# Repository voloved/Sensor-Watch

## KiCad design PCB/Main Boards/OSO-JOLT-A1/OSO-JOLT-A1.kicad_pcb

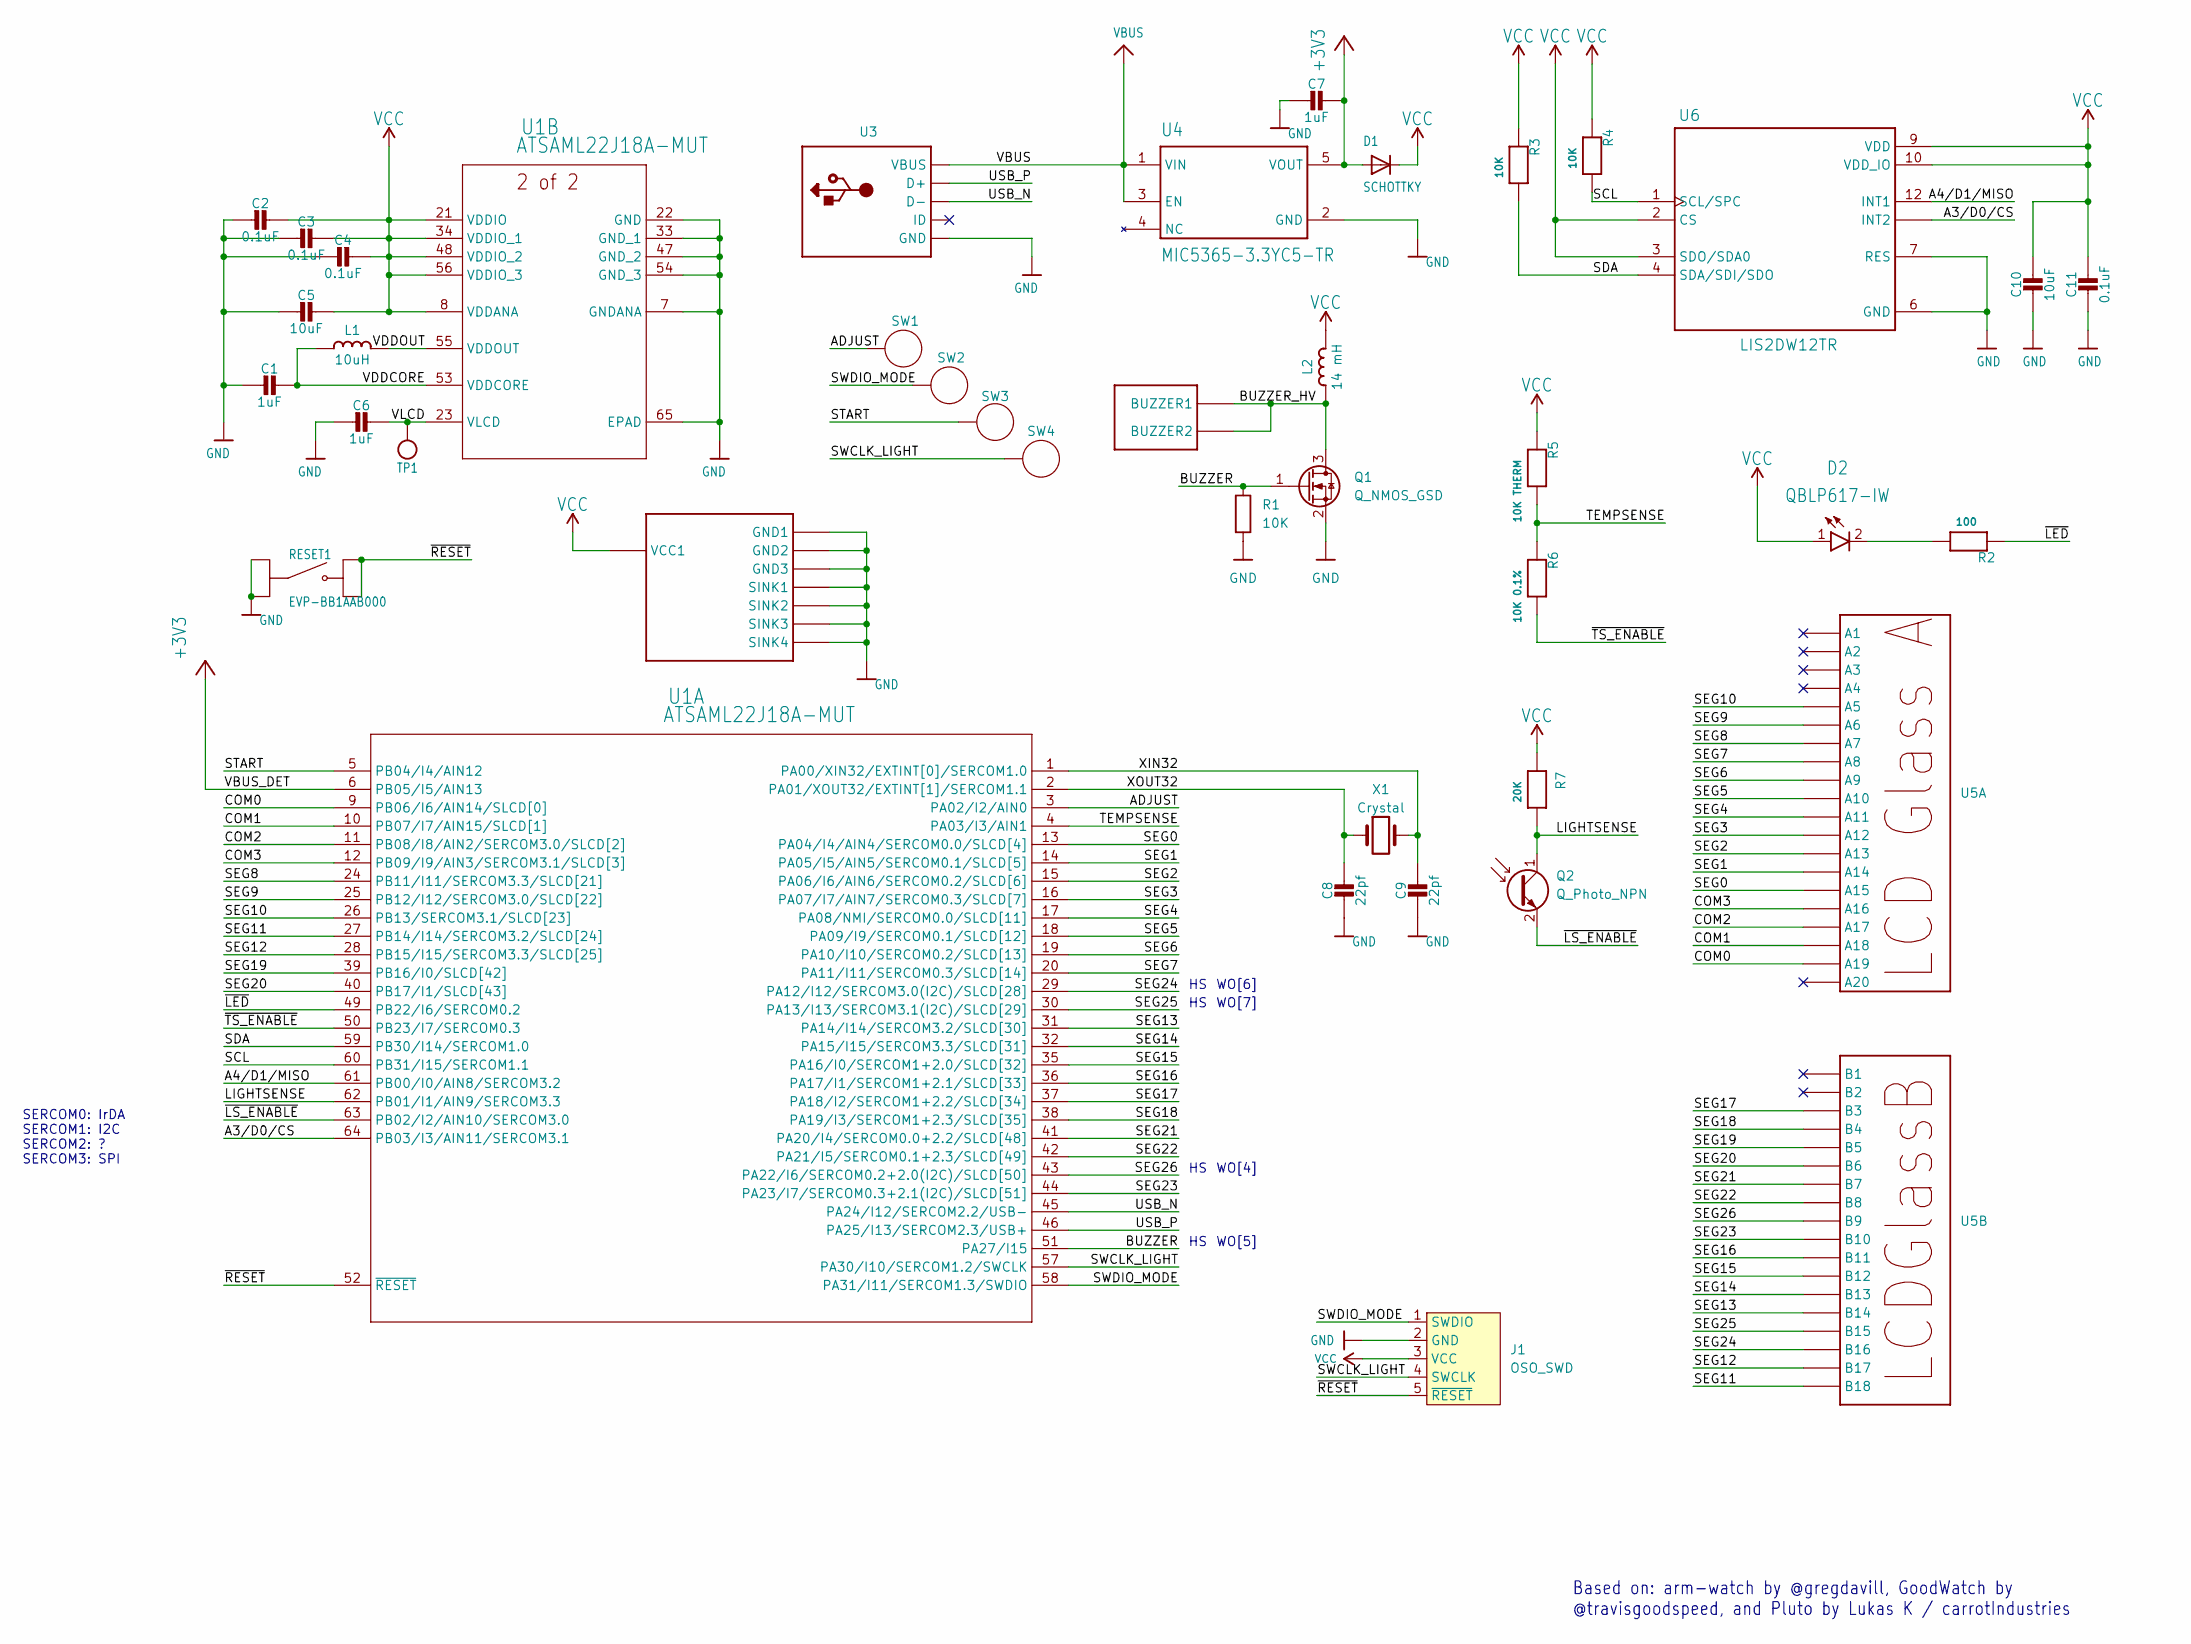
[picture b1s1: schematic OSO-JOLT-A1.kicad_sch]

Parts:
C1: 1uF; C_0805_2012Metric
C2, C4, C11: 0.1uF; C_0603_1608Metric
C3: 0.1uF; C_0201_0603Metric
C5, C10: 10uF; C_0603_1608Metric
C6, C7: 1uF; C_0603_1608Metric
C8, C9: 22pf; C_0402_1005Metric
D1: SCHOTTKY; SOD-323F
D2: QBLP617-IW; LED_QBLP617
J1: OSO_SWD; OSO_SWD_2x3
L1: 10uH; L_0805_2012Metric
L2: 14 mH; ELT3KN
Q1: Q_NMOS_GSD; SOT-523
Q2: Q_Photo_NPN; R_0603_1608Metric
R1, R3, R4: 10K; R_0201_0603Metric
R2: 100; R_0805_2012Metric
R5: 10K THERM; R_0603_1608Metric
R6: 10K 0.1%; R_0603_1608Metric
R7: 20K; R_0201_0603Metric
RESET1: EVP-BB1AAB000; SW_EVP-BB1AAB000
SW1, SW2, SW3, SW4: CASIO-DW5600-BTN
TP1: MICROBUILDER_TESTPOINTROUND1.5MM; MICROBUILDER_TESTPOINT_ROUND_1.5MM
U1: ATSAML22J18A-MUT; QFN64_9X9MC_MCH
U2: CASIO-DW5600-PWR-BUZZER
U3: CASIO-DW5600-USB
U4: MIC5365-3.3YC5-TR; SOT65P210X110-5N
U5: CASIO-DW5600-LCD
U6: LIS2DW12TR; LGA12R50P4X4_200X200X70
X1: Crystal; Crystal_SMD_3215-2Pin_3.2x1.5mm

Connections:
+3V3: C7.1, D1.A, U1.6 (PB05/I5/AIN13), U4.5 (VOUT)
/A3/D0/CS: U1.64 (PB03/I3/AIN11/SERCOM3.1), U6.11 (INT2)
/A4/D1/MISO: U1.61 (PB00/I0/AIN8/SERCOM3.2), U6.12 (INT1)
/ADJUST: SW1.BTN, U1.3 (PA02/I2/AIN0)
/BUZZER: Q1.1 (G), R1.1, U1.51 (PA27/I15)
/BUZZER_HV: L2.1, Q1.3 (D), U2.BUZZER1, U2.BUZZER2
/COM0: U1.9 (PB06/I6/AIN14/SLCD[0]), U5.A19
/COM1: U1.10 (PB07/I7/AIN15/SLCD[1]), U5.A18
/COM2: U1.11 (PB08/I8/AIN2/SERCOM3.0/SLCD[2]), U5.A17
/COM3: U1.12 (PB09/I9/AIN3/SERCOM3.1/SLCD[3]), U5.A16
/LIGHTSENSE: Q2.1 (C), R7.2, U1.62 (PB01/I1/AIN9/SERCOM3.3)
/SCL: R4.2, U1.60 (PB31/I15/SERCOM1.1), U6.1 (SCL/SPC)
/SDA: R3.2, U1.59 (PB30/I14/SERCOM1.0), U6.4 (SDA/SDI/SDO)
/SEG0: U1.13 (PA04/I4/AIN4/SERCOM0.0/SLCD[4]), U5.A15
/SEG1: U1.14 (PA05/I5/AIN5/SERCOM0.1/SLCD[5]), U5.A14
/SEG2: U1.15 (PA06/I6/AIN6/SERCOM0.2/SLCD[6]), U5.A13
/SEG3: U1.16 (PA07/I7/AIN7/SERCOM0.3/SLCD[7]), U5.A12
/SEG4: U1.17 (PA08/NMI/SERCOM0.0/SLCD[11]), U5.A11
/SEG5: U1.18 (PA09/I9/SERCOM0.1/SLCD[12]), U5.A10
/SEG6: U1.19 (PA10/I10/SERCOM0.2/SLCD[13]), U5.A9
/SEG7: U1.20 (PA11/I11/SERCOM0.3/SLCD[14]), U5.A8
/SEG8: U1.24 (PB11/I11/SERCOM3.3/SLCD[21]), U5.A7
/SEG9: U1.25 (PB12/I12/SERCOM3.0/SLCD[22]), U5.A6
/SEG10: U1.26 (PB13/SERCOM3.1/SLCD[23]), U5.A5
/SEG11: U1.27 (PB14/I14/SERCOM3.2/SLCD[24]), U5.B18
/SEG12: U1.28 (PB15/I15/SERCOM3.3/SLCD[25]), U5.B17
/SEG13: U1.31 (PA14/I14/SERCOM3.2/SLCD[30]), U5.B14
/SEG14: U1.32 (PA15/I15/SERCOM3.3/SLCD[31]), U5.B13
/SEG15: U1.35 (PA16/I0/SERCOM1+2.0/SLCD[32]), U5.B12
/SEG16: U1.36 (PA17/I1/SERCOM1+2.1/SLCD[33]), U5.B11
/SEG17: U1.37 (PA18/I2/SERCOM1+2.2/SLCD[34]), U5.B3
/SEG18: U1.38 (PA19/I3/SERCOM1+2.3/SLCD[35]), U5.B4
/SEG19: U1.39 (PB16/I0/SLCD[42]), U5.B5
/SEG20: U1.40 (PB17/I1/SLCD[43]), U5.B6
/SEG21: U1.41 (PA20/I4/SERCOM0.0+2.2/SLCD[48]), U5.B7
/SEG22: U1.42 (PA21/I5/SERCOM0.1+2.3/SLCD[49]), U5.B8
/SEG23: U1.44 (PA23/I7/SERCOM0.3+2.1(I2C)/SLCD[51]), U5.B10
/SEG24: U1.29 (PA12/I12/SERCOM3.0(I2C)/SLCD[28]), U5.B16
/SEG25: U1.30 (PA13/I13/SERCOM3.1(I2C)/SLCD[29]), U5.B15
/SEG26: U1.43 (PA22/I6/SERCOM0.2+2.0(I2C)/SLCD[50]), U5.B9
/START: SW3.BTN, U1.5 (PB04/I4/AIN12)
/SWCLK_LIGHT: J1.4 (SWCLK), SW4.BTN, U1.57 (PA30/I10/SERCOM1.2/SWCLK)
/SWDIO_MODE: J1.1 (SWDIO), SW2.BTN, U1.58 (PA31/I11/SERCOM1.3/SWDIO)
/TEMPSENSE: R5.2, R6.1, U1.4 (PA03/I3/AIN1)
/USB_N: U1.45 (PA24/I12/SERCOM2.2/USB-), U3.USB_N (D-)
/USB_P: U1.46 (PA25/I13/SERCOM2.3/USB+), U3.USB_P (D+)
/VDDCORE: C1.1, L1.1, U1.53 (VDDCORE)
/VDDOUT: L1.2, U1.55 (VDDOUT)
/VLCD: C6.1, TP1.P$1, U1.23 (VLCD)
/XIN32: C9.1, U1.1 (PA00/XIN32/EXTINT[0]/SERCOM1.0), X1.2
/XOUT32: C8.1, U1.2 (PA01/XOUT32/EXTINT[1]/SERCOM1.1), X1.1
/~LED: R2.1, U1.49 (PB22/I6/SERCOM0.2)
/~LS_ENABLE: Q2.2 (E), U1.63 (PB02/I2/AIN10/SERCOM3.0)
/~RESET: J1.5 (~RESET), RESET1.B1, RESET1.B2, U1.52 (~RESET)
/~TS_ENABLE: R6.2, U1.50 (PB23/I7/SERCOM0.3)
GND: C1.2, C2.2, C3.2, C4.2, C5.2, C6.2, C7.2, C8.2, C9.2, C10.2, C11.2, J1.2 (GND), Q1.2 (S), R1.2, RESET1.A1, RESET1.A2, U1.7 (GNDANA), U1.22 (GND), U1.33 (GND_1), U1.47 (GND_2), U1.54 (GND_3), U1.65 (EPAD), U2.GND1, U2.GND2, U2.GND3, U2.SINK1, U2.SINK2, U2.SINK3, U2.SINK4, U3.GND, U4.2 (GND), U6.6 (GND), U6.7 (RES), U6.8 (GND)
unnamed: D2.2 (C), R2.2
VBUS: U3.VBUS, U4.1 (VIN), U4.3 (EN)
VCC: C2.1, C3.1, C4.1, C5.1, C10.1, C11.1, D1.C, D2.1 (A), J1.3 (VCC), L2.2, R3.1, R4.1, R5.1, R7.1, U1.8 (VDDANA), U1.21 (VDDIO), U1.34 (VDDIO_1), U1.48 (VDDIO_2), U1.56 (VDDIO_3), U2.VCC1, U6.2 (CS), U6.3 (SDO/SDA0), U6.9 (VDD), U6.10 (VDD_IO)

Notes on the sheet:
Based on: arm-watch by @gregdavill, GoodWatch by @travisgoodspeed, and Pluto by Lukas K / carrotIndustries
WO[7]
SERCOM0: IrDA SERCOM1: I2C SERCOM2: ? SERCOM3: SPI
WO[6]
WO[4]
WO[5]

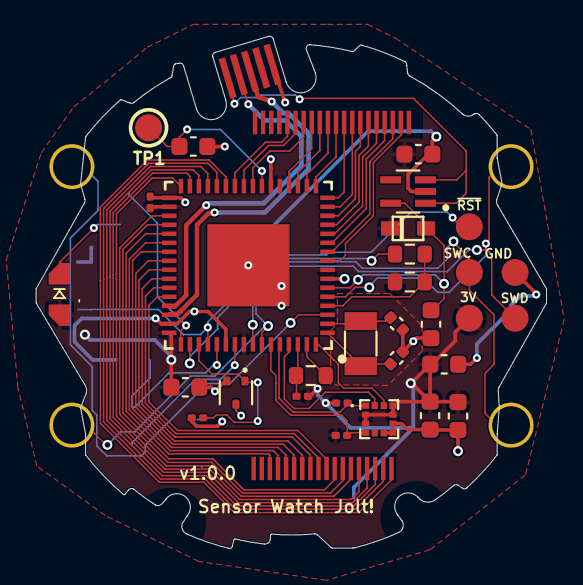
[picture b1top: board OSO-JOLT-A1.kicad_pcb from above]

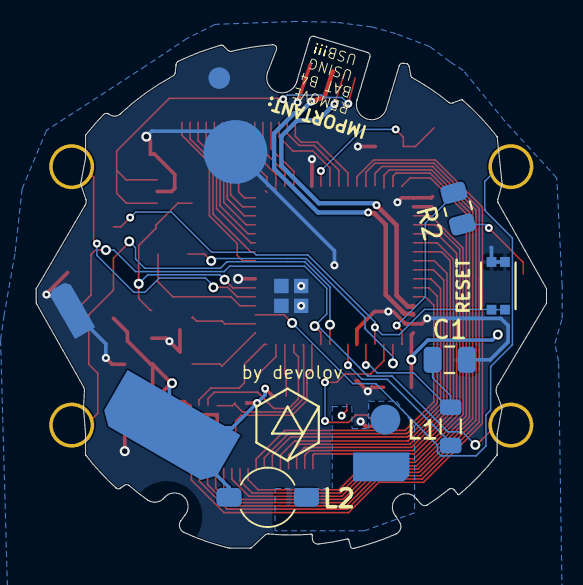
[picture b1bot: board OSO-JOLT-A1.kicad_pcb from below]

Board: 2 copper layers, 28.3 x 28.5 mm, 38 parts (5 on the bottom side), 59 nets.

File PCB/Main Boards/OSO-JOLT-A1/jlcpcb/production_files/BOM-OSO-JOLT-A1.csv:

Comment,Designator,Footprint,LCSC,Quantity
0.1uF,"C11,C2,C4",C_0603_1608Metric,C127833,3
0.1uF,C3,C_0201_0603Metric,C85923,1
100,R2,R_0805_2012Metric,C445646,1
10K,"R1,R3,R4",R_0201_0603Metric,C717002,3
10K 0.1%,R6,R_0603_1608Metric,C190610,1
10K THERM,R5,R_0603_1608Metric,C236277,1
10uF,"C10,C5",C_0603_1608Metric,C77040,2
10uH,L1,L_0805_2012Metric,C88172,1
14 mH,L2,ELT3KN,C20012585,1
1uF,C1,C_0805_2012Metric,C116352,1
1uF,"C6,C7",C_0603_1608Metric,C2167386,2
20K,R7,R_0201_0603Metric,C190611,1
22pf,"C8,C9",C_0402_1005Metric,C126502,2
ATSAML22J18A-MUT,U1,QFN64_9X9MC_MCH,C618315,1
Crystal,X1,Crystal_SMD_3215-2Pin_3.2x1.5mm,C2450269,1
EVP-BB1AAB000,RESET1,SW_EVP-BB1AAB000,C5185477,1
LIS2DW12TR,U6,LGA12R50P4X4_200X200X70,C189624,1
MIC5365-3.3YC5-TR,U4,SOT65P210X110-5N,C73103,1
QBLP617-IW,D2,LED_QBLP617,C7329223,1
Q_NMOS_GSD,Q1,SOT-523,C509959,1
Q_Photo_NPN,Q2,R_0603_1608Metric,C131276,1
SCHOTTKY,D1,SOD-323F,C119617,1

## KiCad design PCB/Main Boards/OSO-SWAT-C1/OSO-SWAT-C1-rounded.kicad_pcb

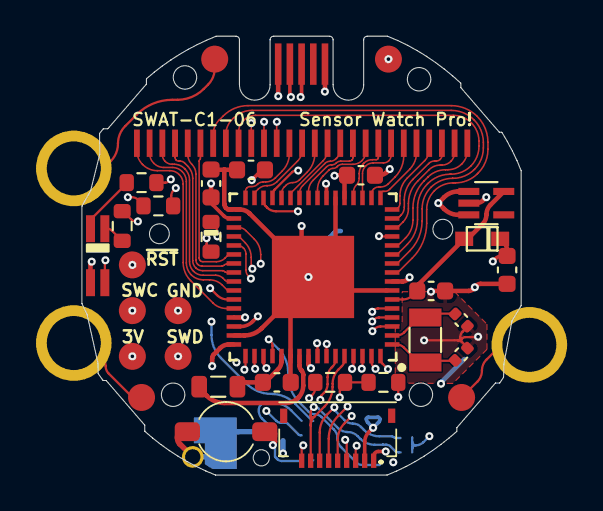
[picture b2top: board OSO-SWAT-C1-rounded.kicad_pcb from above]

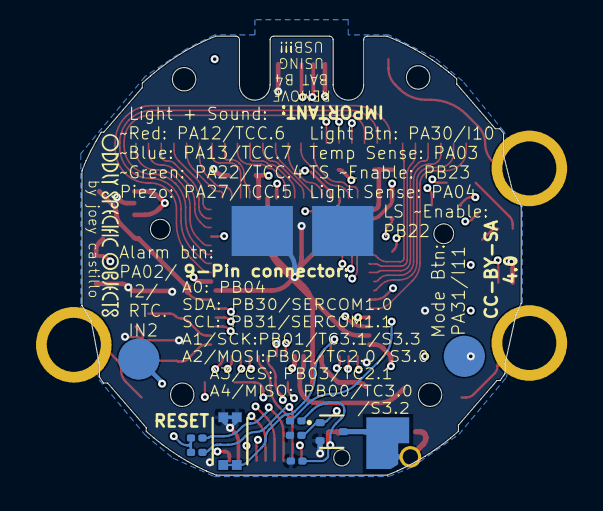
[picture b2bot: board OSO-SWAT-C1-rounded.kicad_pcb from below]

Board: 4 copper layers, 24.4 x 24.4 mm, 35 parts (7 on the bottom side), 61 nets.

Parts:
C1: 10uF; C_0603_1608Metric
C2: 0.1uF; C_0201_0603Metric
C3, C4: 0.1uF; C_0603_1608Metric
C5, C6, C9: 1uF; C_0603_1608Metric
C7, C8: 22pf; C_0402_1005Metric
D1: SCHOTTKY; SOD-323F
D2: QBLP655-RGB; LED_QBLP655_RGB
J1: OSO_SWD; OSO_SWD_2x3
J2: FH19C-9S-0.5SH_10_; FH19C9S05SH10
L1: 10uH; L_0805_2012Metric
L2: 14 mH; ELT3KN
Q1: Q_Photo_NPN; R_0603_1608Metric
Q2: Q_NMOS_GSD; SOT-523
R1, R2, R3, R4: 10K; R_0201_0603Metric
R6: 1K; R_0603_1608Metric
R7, R8: 100; R_0603_1608Metric
R10: 10K THERM; R_0603_1608Metric
R11: 10K 0.1%; R_0603_1608Metric
RESET0: EVP-BB1AAB000; SW_EVP-BB1AAB000
TP1, TP8, TP9, TP10: MICROBUILDER_TESTPOINTROUND1.5MM; MICROBUILDER_TESTPOINT_ROUND_1.5MM
U1: ATSAML22J18A-MUT; QFN64_9X9MC_MCH
U2: MIC5365-3.3YC5-TR; SOT65P210X110-5N
U$2: SENSOR-WATCH-USB; CASIO-F91W-OUTLINE-USB
X1: Crystal; Crystal_SMD_3215-2Pin_3.2x1.5mm

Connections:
+3V3: C9.1, D1.A, U1.6 (PB05/I5/AIN13), U2.5 (VOUT)
/A0: J2.9, U1.5 (PB04/I4/AIN12)
/A1_SCK: J2.6, U1.62 (PB01/I1/AIN9/SERCOM3.3)
/A2_MOSI: J2.5, U1.63 (PB02/I2/AIN10/SERCOM3.0)
/A3/D0/CS: J2.4, U1.64 (PB03/I3/AIN11/SERCOM3.1)
/A4/D1/MISO: J2.3, U1.61 (PB00/I0/AIN8/SERCOM3.2)
/ALARM: TP10.P$1, U1.3 (PA02/I2/AIN0), U$2.ALARM
/BUZZER: Q2.1 (G), R2.1, U1.51 (PA27/I15)
/BUZZER_HV: L2.1, Q2.3 (D), U$2.BUZZER
/COM0: U1.9 (PB06/I6/AIN14/SLCD[0]), U$2.7
/COM1: U1.10 (PB07/I7/AIN15/SLCD[1]), U$2.8
/COM2: U1.11 (PB08/I8/AIN2/SERCOM3.0/SLCD[2]), U$2.9
/LIGHTSENSE: Q1.1 (C), R1.2, U1.13 (PA04/I4/AIN4/SERCOM0.0/SLCD[4])
/SCL: J2.8, R3.2, U1.60 (PB31/I15/SERCOM1.1)
/SDA: J2.7, R4.2, U1.59 (PB30/I14/SERCOM1.0)
/SEG0: U1.12 (PB09/I9/AIN3/SERCOM3.1/SLCD[3]), U$2.27
/SEG1: U1.14 (PA05/I5/AIN5/SERCOM0.1/SLCD[5]), U$2.26
/SEG2: U1.15 (PA06/I6/AIN6/SERCOM0.2/SLCD[6]), U$2.25
/SEG3: U1.16 (PA07/I7/AIN7/SERCOM0.3/SLCD[7]), U$2.24
/SEG4: U1.17 (PA08/NMI/SERCOM0.0/SLCD[11]), U$2.23
/SEG5: U1.18 (PA09/I9/SERCOM0.1/SLCD[12]), U$2.22
/SEG6: U1.19 (PA10/I10/SERCOM0.2/SLCD[13]), U$2.21
/SEG7: U1.20 (PA11/I11/SERCOM0.3/SLCD[14]), U$2.20
/SEG8: U1.24 (PB11/I11/SERCOM3.3/SLCD[21]), U$2.19
/SEG9: U1.25 (PB12/I12/SERCOM3.0/SLCD[22]), U$2.18
/SEG10: U1.26 (PB13/SERCOM3.1/SLCD[23]), U$2.17
/SEG11: U1.27 (PB14/I14/SERCOM3.2/SLCD[24]), U$2.16
/SEG12: U1.28 (PB15/I15/SERCOM3.3/SLCD[25]), U$2.15
/SEG13: U1.31 (PA14/I14/SERCOM3.2/SLCD[30]), U$2.14
/SEG14: U1.32 (PA15/I15/SERCOM3.3/SLCD[31]), U$2.13
/SEG15: U1.35 (PA16/I0/SERCOM1+2.0/SLCD[32]), U$2.12
/SEG16: U1.36 (PA17/I1/SERCOM1+2.1/SLCD[33]), U$2.11
/SEG17: U1.37 (PA18/I2/SERCOM1+2.2/SLCD[34]), U$2.10
/SEG18: U1.38 (PA19/I3/SERCOM1+2.3/SLCD[35]), U$2.6
/SEG19: U1.39 (PB16/I0/SLCD[42]), U$2.5
/SEG20: U1.40 (PB17/I1/SLCD[43]), U$2.4
/SEG21: U1.41 (PA20/I4/SERCOM0.0+2.2/SLCD[48]), U$2.3
/SEG22: U1.42 (PA21/I5/SERCOM0.1+2.3/SLCD[49]), U$2.2
/SEG23: U1.44 (PA23/I7/SERCOM0.3+2.1(I2C)/SLCD[51]), U$2.1
/SWCLK_LIGHT: J1.4 (SWCLK), TP8.P$1, U1.57 (PA30/I10/SERCOM1.2/SWCLK), U$2.LIGHT
/SWDIO_MODE: J1.1 (SWDIO), TP9.P$1, U1.58 (PA31/I11/SERCOM1.3/SWDIO), U$2.MODE
/TEMPSENSE: R10.2, R11.1, U1.4 (PA03/I3/AIN1)
/USB_N: U1.45 (PA24/I12/SERCOM2.2/USB-), U$2.USB_N (D-)
/USB_P: U1.46 (PA25/I13/SERCOM2.3/USB+), U$2.USB_P (D+)
/VDDCORE: C5.1, L1.1, U1.53 (VDDCORE)
/VDDOUT: L1.2, U1.55 (VDDOUT)
/VLCD: C6.1, TP1.P$1, U1.23 (VLCD)
/XIN32: C7.1, U1.1 (PA00/XIN32/EXTINT[0]/SERCOM1.0), X1.2
/XOUT32: C8.1, U1.2 (PA01/XOUT32/EXTINT[1]/SERCOM1.1), X1.1
/~BLUE: R8.1, U1.30 (PA13/I13/SERCOM3.1(I2C)/SLCD[29])
/~GREEN: R6.1, U1.43 (PA22/I6/SERCOM0.2+2.0(I2C)/SLCD[50])
/~LS_ENABLE: Q1.2 (E), U1.49 (PB22/I6/SERCOM0.2)
/~RED: R7.1, U1.29 (PA12/I12/SERCOM3.0(I2C)/SLCD[28])
/~RESET: J1.5 (~RESET), RESET0.B1, RESET0.B2, U1.52 (~RESET)
/~TS_ENABLE: R11.2, U1.50 (PB23/I7/SERCOM0.3)
GND: C1.2, C2.2, C3.2, C4.2, C5.2, C6.2, C7.2, C8.2, C9.2, J1.2 (GND), J2.2, Q2.2 (S), R2.2, RESET0.A1, RESET0.A2, U1.7 (GNDANA), U1.22 (GND), U1.33 (GND_1), U1.47 (GND_2), U1.54 (GND_3), U1.65 (EPAD), U2.2 (GND), U$2.GND, U$2.GND1, U$2.GND2
unnamed: D2.1 (CR), R7.2
unnamed: D2.4 (CG), R6.2
unnamed: D2.3 (CB), R8.2
VBUS: U2.1 (VIN), U2.3 (EN), U$2.VBUS
VCC: C1.1, C2.1, C3.1, C4.1, D1.C, D2.2 (A), J1.3 (VCC), J2.1, L2.2, R1.1, R3.1, R4.1, R10.1, U1.8 (VDDANA), U1.21 (VDDIO), U1.34 (VDDIO_1), U1.48 (VDDIO_2), U1.56 (VDDIO_3), U$2.VCC1, U$2.VCC2

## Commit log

2024-06-30 probabilty face maintains its previous preset; tally face can decrement by 10 by holding LED button
2025-03-15 DST check occurs when waking watch from sleep.
2025-03-15 Added gerber files to gitignore
2025-03-24 Prepped Festival Face for Lolapalooza 2025
2025-04-23 Caches the sunrise and set time and only refreshes it if needed
2025-05-11 Made Deep Sleep timeout 4 hours and it'll reset if the temperature the temp face sees is above the minimum anytime in between.
2025-05-19 Added festival face to ternary display
2025-05-20 Added ü (used in place of ;)
2025-05-20 Added isDaytime in settings
2025-05-20 Modified chime logic on other clock faces
2025-05-20 Updated default alarm settings
2025-05-21 Don't go into LE at night; is_daytime logic only runs at top of hour.
2025-05-21 Inverted isdaylight logic
2025-05-22 is_daytime updates at the start of the hour
2025-06-04 Fixed using prev sunset info
2025-06-06 Fallback will be previous result since it'll likely usually be good enough
2025-06-06 Removed second festival face
2025-06-23 Decrementing deep sleep will not reset due to a chime
2025-06-28 Removed background task on party face when resigning
2025-07-05 Fix in chiming when one segment is set to chime and the other isn't for simple clock
2025-07-05 Modified the rest of the watch faces to follow the same logic as the prev commit
2025-07-06 Updated some default settings
2025-07-06 LCD doesn't refresh if it's on
2025-07-26 Festival face is second face in prep for Lolla
2025-07-29 Negative numbers in Tally display in center
2025-08-06 Moved Festival face back now that the festival is over
2025-08-20 Voltage face now logs
2025-08-20 Can loop back on moon phase
2025-08-20 Changed LED mapping logic
2025-08-20 Moved some faces around
2025-08-23 Loop ternary faces that don't use dfault loop
2025-08-24 Voltage face now updates every 5 seconds
2025-12-21 deploy: 8c39d428247edba25ee17bcb45a4c919b4466d71
2025-12-21 Added Sensorwatch Pro PCB
2026-02-21 Began making jolt pcb
2026-02-22 Added pads
2026-02-22 Began routing
2026-02-24 Added keepouts on footprint
2026-02-24 Laying out components
2026-02-24 Pre-routing commit
2026-02-24 Began routing and added courtyard for light bracket
2026-02-24 Seperate DW5600 components and made the edge cuts live on thepcb
2026-02-25 Resynced pcb and sch
2026-02-26 end of day routing commit
2026-02-27 Added all footprints
2026-02-27 Began adding accelerometer board directly on PCB
2026-02-27 Revert "Began adding accelerometer board directly on PCB"
    This reverts commit 8b1a0a982f9e72f020d5a62f3937e948766a17b7.
2026-02-27 All components placed in hopefully final location
2026-02-28 Finished first pass at routing
2026-02-28 Made board 2 layer for 0.4mm thickness
2026-03-02 Made back components larger in case I want to hand-solder them
2026-03-08 Added Gerber files
2026-03-08 Modified NMOS to match the one on the Pro
2026-03-18 Removed the daughterboard connector and placed LIS2DW directly on board
2026-03-18 This commit is what holds the design sent to JLCPCB
2026-03-19 Just kidding about the previous commit, this one gives the correct pn to C11 and is what was sent for build

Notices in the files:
PCB/Main Boards/OSO-SWAT-C1/OSO-SWAT-C1-rounded.kicad_pcb:
CC-BY-SA
